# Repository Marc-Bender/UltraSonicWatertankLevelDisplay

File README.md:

# README

##Intended Usecase
Waterlevel display in multitank battey of tanks. Tanks are located in basement, sense device will be mounted on top of tanks far enough away from filling port. 
Thus no watertightness or waterresistance is implemented for any of the components.

## Design Features
Multiple Sensorboards "supported" by design (read Mistakes#J5 for more).
Elaborate Liter-age estimation algorithm by approximation of tank geometry with multiple boxes of varying area, spacing of estimation-box-area-entries parametrizable (1 global value)
Remaining Tankgeometry (Distance when full, distance when empty, number of tanks) parametrizable. 
Measurement sample averaging with parametrizable sample count for general stability, reproducability and compensation of effects of surface-waves while filling (effectiveness not proven)
Sleep modes for powersaving: between user interactions (deepest possible sleep mode), for time that display is supposed to be on (deepest sleep mode that can be left by timer)
Parametrization via UART with ready made tool (Open protocol)

## Operating instructions
Connect battery without pressing the front panel button --> normal startup procedure; system will perform one measurement cycle and show the results on the display
Connect battery with pressed front panel button --> boot into parametrization mode; leave via UART command or powercycle

## Basic-most Troubleshooting 
### "Display stays dark on button press"
Disassembly of sense device, check battery voltage -- system will not attempt any measurements below 7V
When Battery Voltage >7V attempt powercycle (battery disconnect-reconnect)

## Parametrization protocol
### UART Specifics
9600Baud, 8bits, 1 stop bit, no parity
### Leaving the parametrization session
send ":q" (without quotes)
### write a memory location 
send ":wXXYY" where XX is the address in MSB first and YY is the value in MSB first (both 16bit); device will respond with ":WXX00" where XX is that same address and 00 is padding data.
### read a memory location
analogous to write except ":r" is to be used instead of ":w"; data will be in last two response bytes in 16bit MSBFirst
### Memory Map
TankFullCM         | 0x0000 | 2bytes
TankEmptyCM        | 0x0002 | 2bytes
NumTanks           | 0x0004 | 1byte
AreaEntryCount     | 0x0005 | 1byte
AreaEntrySpacingCm | 0x0006 | 1byte
AveragingCount     | 0x0007 | 1byte
SensorType         | 0x0008 | 1byte (0: HC-SR04, 1:Grove)
AreaEntrySpaceStart| 0x000A | 2bytes per entry

## Power Figures
To be powered from a 9V Block Battery. Active current (w/ Display on, sensor not attached) is ~15mA. 
The MCU will be in sleep just about the entire time. The current transient for the MCU being active is assumed to be neglegdable.
The current transient by the sensor has not been determined. But the sensor is powered from IO Pins and normally unpowered thus not adding to the Iq.
The current consumption in sleep (Display off, sensor disconnected, MCU sleep) was in the noise of the multimeter (readings are typical at ~1mV across 10R shunt experimentally put in place instead of regulator; ~100uA)

## Hacking features
Default values for liter estimation algorithm when activated by define but not configured in EEPROM.
Define for circumventing the Battery voltage measurement evaluation -- effectively rendering the BatteryLowFault State inoperable/unreachable.

## Mistakes 

### Parametrization tool 

Somehow the parametrization did not work in the real usecase where the device is powered from a 9V battery; neither with connected gnd nor with connected 5V rail nor both connected (to the usb to serial brigde)
Parametrization also did not work no matter if the TX and RX lines are crossed or not. -- I did not feel like investing any time in this issue anymore, thus did not use the parametrization at all and hardcoded the tank geometry
Circumvent: recompile firmware with different values for each tank geometry or manually generate the eeprom file. 

### voltage measurement 

The battery voltage measurement is wildly off -- this may be down to the reference of the ADC (VCCA) not being measured in any way impacting the measured value...
Circumvent: none

### case design / Assembly design 

the screw holes for the display retainment screws should not have gone through the entire part. 
the Controller PCB should have had any mounting holes. 
The PCB Sandwich should be held in place on the button side as well in some way; solved by drilling through the PCB (somewhere in the gnd plane above the button) and into the frontplate then securing the pcb sandwich with 1 or 2 threads of a screw
The button actuator may collide with the PCB sandwich and should be reshaped.
The Parametrization header's 5V pin is obscured by the lower mounting hole of the display -> circumvent by snipping that off.

### Q5
Reverse voltage Protection "Diode" Transistor (Q5) did not work in my testing.
Circumvent by placing a ordinary diode between pins 1 and 2 of the footprint.

### U2
Was not available to me at the time of building and pinning is unlike 117 or 78xx series regulator thus the device may be a bad pick when a generic jellybean part would be wanted. 
There is no special reason to use this one. 
Circumvent by either buying appropriate part or replace with 7805 mounted in reverse (smaller footprint one will work as current consumption of MCU and display when active is ~15mA in my measurement thus anysize regulator will likely be enough)

### J1
/tRST is connected to MCU but /sRST would be the one to use with standard AVR JTAG pinout. 
Circumvent by either using SPI which is available on the Display header or by shorting the /tRST and /sRST pins together.

### U1
ATmega1284P was initially designed in as it happened to be in my junkbox... later replaced with ATmega324PB as a cheaper more than plenty replacement.
The ATmega324PB is not exactly pin compatible as the two (1284P) supply pins on the bottom edge (17, 18) are IO pins on the 324PB.
Circumvent: none
Fix: new layout or stick with original design MCU. 
Impact: none as long as the SW does not configure the two pins as outputs (which it should not -- by design)

### V0
V0 had been planned to be connected to resistor divider for contrast setting (that is switch-off-able). But fixed 1k pull down would be enough.
Circumvent by not placing R13, R14, R11, Q3 and instead placing R12 as ~500R and placing another ~500R between pins 2 and 3 of Q3 (slight cant).
alternatively only place R12 as 1k and bridge pins 2 and 3 of Q3

### J5 
Pinning of header for Grove Ultrasonic rangefinder module is completely messed up w/ regard to the module. 
Circumvent: use a crossover wireharnes and / or change the pinning in as far as possible (supply pins). Possibly bridge pin 3 and 4 on J5 to fix switched signal and NC pin. 
alternatively stick with HC-SR04 board instead. 
Firmware side of things has not been verified for Grove module at all thus it may require some hacking to get working. 

### Q4 
Technically working how ever not sufficent for turning off the display. The display module will get its power also over the data and control lines if not powered thus setting all data and control lines to input-no-pullup before turning off the display is required.
Circumvent: not needed -- already accounted for in Firmware. 

## Issues
### Parametrization tool communication (General)
Send commands multiple times until a) the display lights up [stop session command] or b) message counter in log window in bottom updates
### Parametrization tool connection
Start the sense device in parametrization mode.
Send the stop command from the tool until successfully left the session. 
Keep the Tool running and connected to the UART to USB adapter.
Restart the sense device in parametrization mode. 
The communciation should now work -- signs of a non working communication are UI buttons not changing their animated state.
### Parametrization best practices
Send a value
set a different value
Read back value --> the UI element for setting doubles for display and should change value to before set value.

Always leave the parametrization session by stop command when values have been changed in order for the write to peristant memory to happen.

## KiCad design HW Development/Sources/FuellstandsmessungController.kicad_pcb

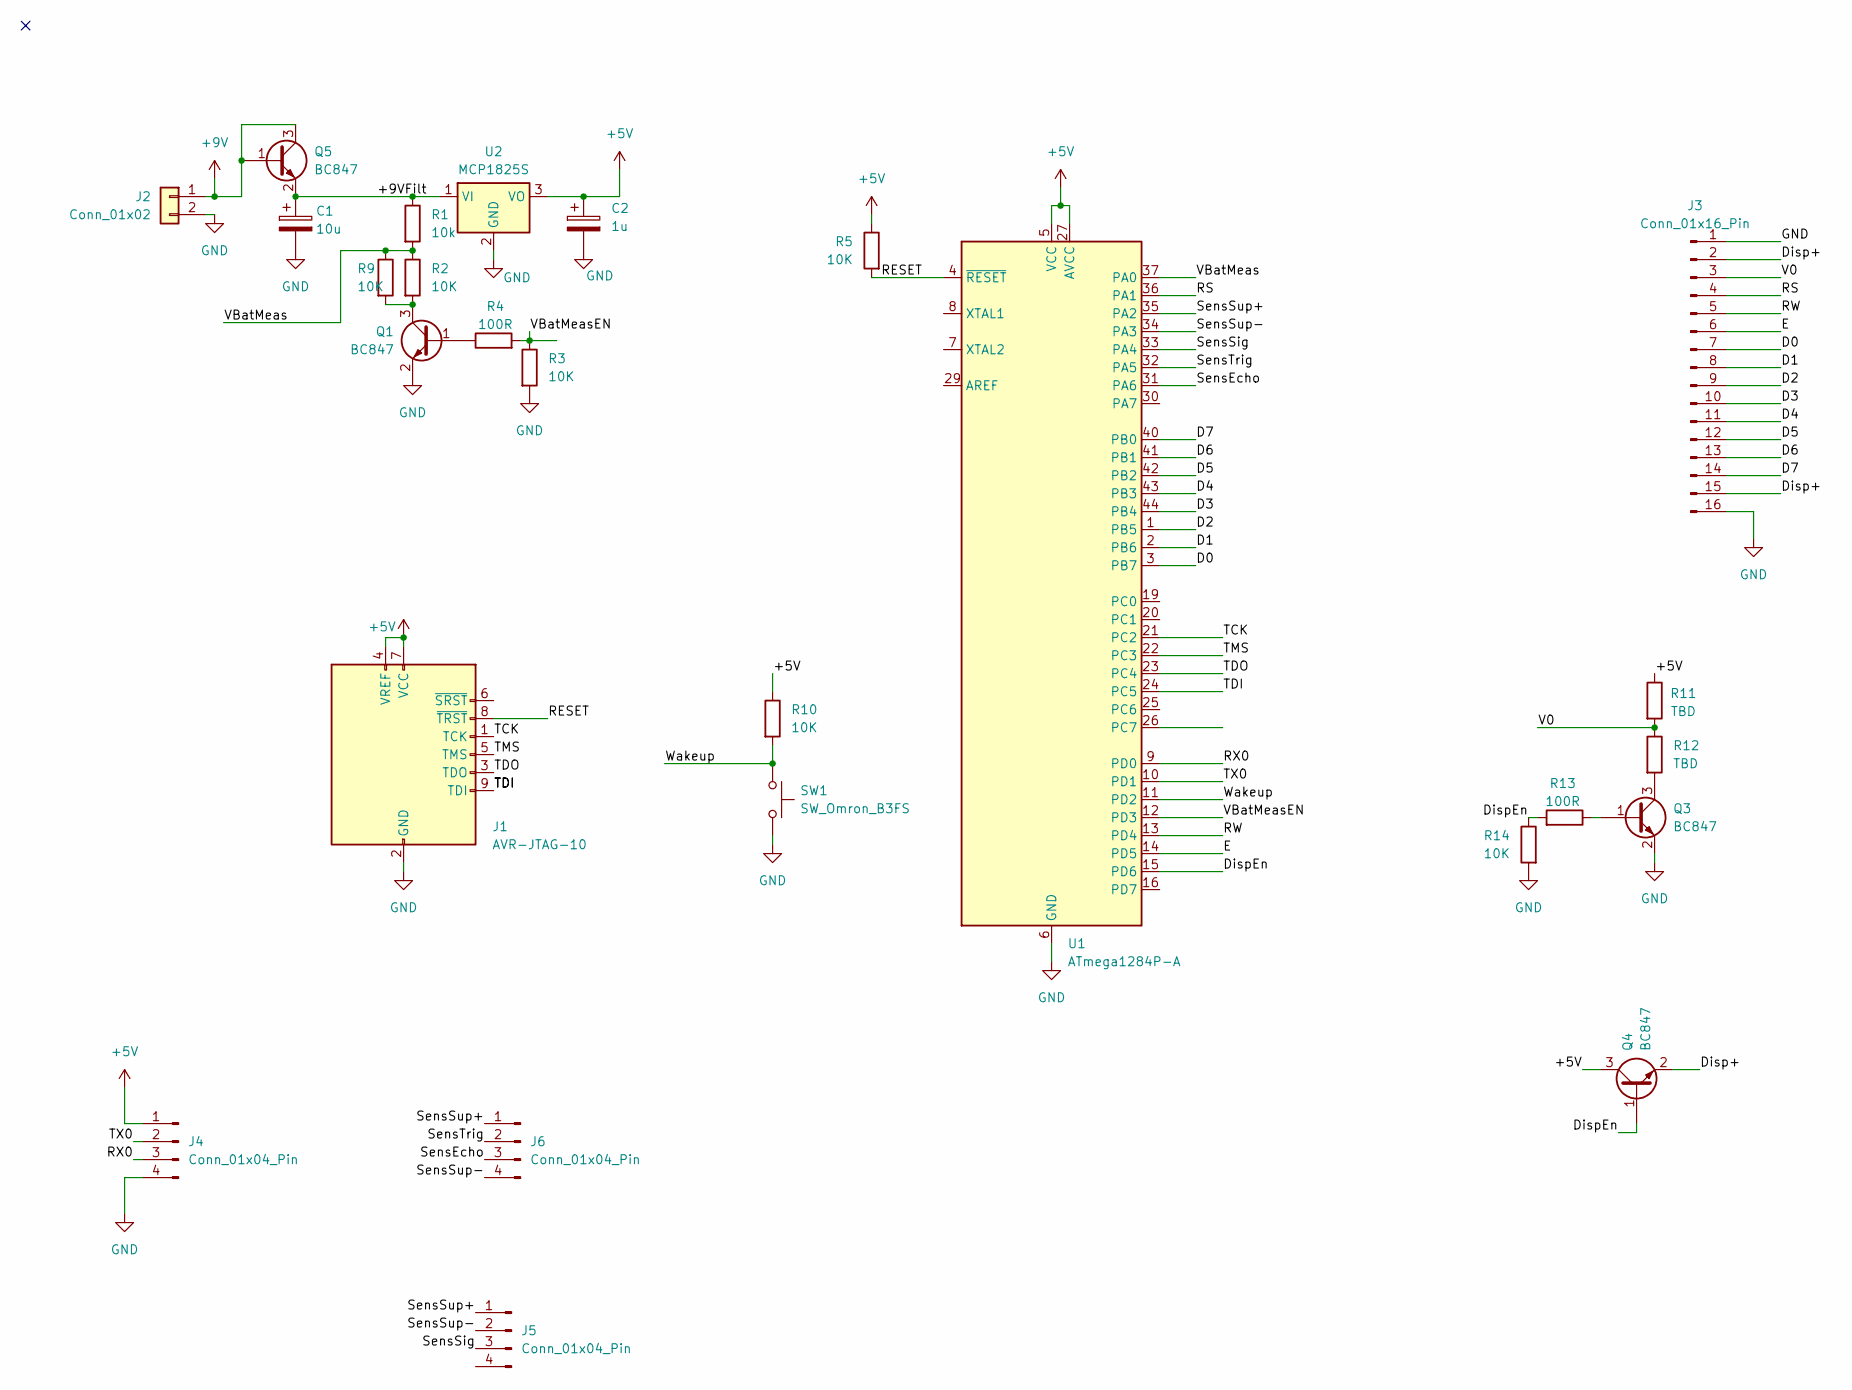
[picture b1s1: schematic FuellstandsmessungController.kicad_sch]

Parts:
C1: 10u; CP_Radial_D5.0mm_P2.50mm
C2: 1u; CP_Radial_D5.0mm_P2.50mm
J1: AVR-JTAG-10; IDC-Header_2x05_P2.54mm_Vertical
J2: Conn_01x02; PinHeader_1x02_P2.54mm_Vertical
J3: Conn_01x16_Pin; PinHeader_1x16_P2.54mm_Vertical
J4, J5, J6: Conn_01x04_Pin; PinHeader_1x04_P2.54mm_Vertical
Q1, Q3, Q4, Q5: BC847; SOT-23
R1: 10k; R_0805_2012Metric_Pad1.20x1.40mm_HandSolder
R2, R3, R5, R9, R10, R14: 10K; R_0805_2012Metric_Pad1.20x1.40mm_HandSolder
R4, R13: 100R; R_0805_2012Metric_Pad1.20x1.40mm_HandSolder
R11, R12: TBD; R_0805_2012Metric_Pad1.20x1.40mm_HandSolder
SW1: SW_Omron_B3FS; SW_SPST_Omron_B3FS-100xP
U1: ATmega1284P-A; TQFP-44_10x10mm_P0.8mm
U2: MCP1825S; SOT-223-3_TabPin2

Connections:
+5V: C2.1, J1.4 (VREF), J1.7 (VCC), J4.1, Q4.3 (C), R5.1, R10.1, R11.1, U1.5 (VCC), U1.17 (VCC), U1.27 (AVCC), U1.38 (VCC), U2.3 (VO)
+9V: J2.1, Q5.1 (B), Q5.3 (C)
/+9VFilt: C1.1, Q5.2 (E), R1.1, U2.1 (VI)
/D0: J3.7, U1.3 (PB7)
/D1: J3.8, U1.2 (PB6)
/D2: J3.9, U1.1 (PB5)
/D3: J3.10, U1.44 (PB4)
/D4: J3.11, U1.43 (PB3)
/D5: J3.12, U1.42 (PB2)
/D6: J3.13, U1.41 (PB1)
/D7: J3.14, U1.40 (PB0)
/Disp+: J3.2, J3.15, Q4.2 (E)
/DispEn: Q4.1 (B), R13.2, R14.1, U1.15 (PD6)
/E: J3.6, U1.14 (PD5)
/RESET: J1.8 (~TRST), R5.2, U1.4 (~RESET)
/RS: J3.4, U1.36 (PA1)
/RW: J3.5, U1.13 (PD4)
/RX0: J4.3, U1.9 (PD0)
/SensEcho: J6.3, U1.31 (PA6)
/SensSig: J5.3, U1.33 (PA4)
/SensSup+: J5.1, J6.1, U1.35 (PA2)
/SensSup-: J5.2, J6.4, U1.34 (PA3)
/SensTrig: J6.2, U1.32 (PA5)
/TCK: J1.1 (TCK), U1.21 (PC2)
/TDI: J1.9 (TDI), U1.24 (PC5)
/TDO: J1.3 (TDO), U1.23 (PC4)
/TMS: J1.5 (TMS), U1.22 (PC3)
/TX0: J4.2, U1.10 (PD1)
/V0: J3.3, R11.2, R12.1
/VBatMeas: R1.2, R2.1, R9.1, U1.37 (PA0)
/VBatMeasEN: R3.1, R4.2, U1.12 (PD3)
/Wakeup: R10.2, SW1.1, U1.11 (PD2)
GND: C1.2, C2.2, J1.2 (GND), J1.10 (GND), J2.2, J3.1, J3.16, J4.4, Q1.2 (E), Q3.2 (E), R3.2, R14.2, SW1.2, U1.6 (GND), U1.18 (GND), U1.28 (GND), U1.39 (GND), U2.2 (GND)
unnamed: Q1.1 (B), R4.1
unnamed: Q1.3 (C), R2.2, R9.2
unnamed: Q3.1 (B), R13.1
unnamed: Q3.3 (C), R12.2

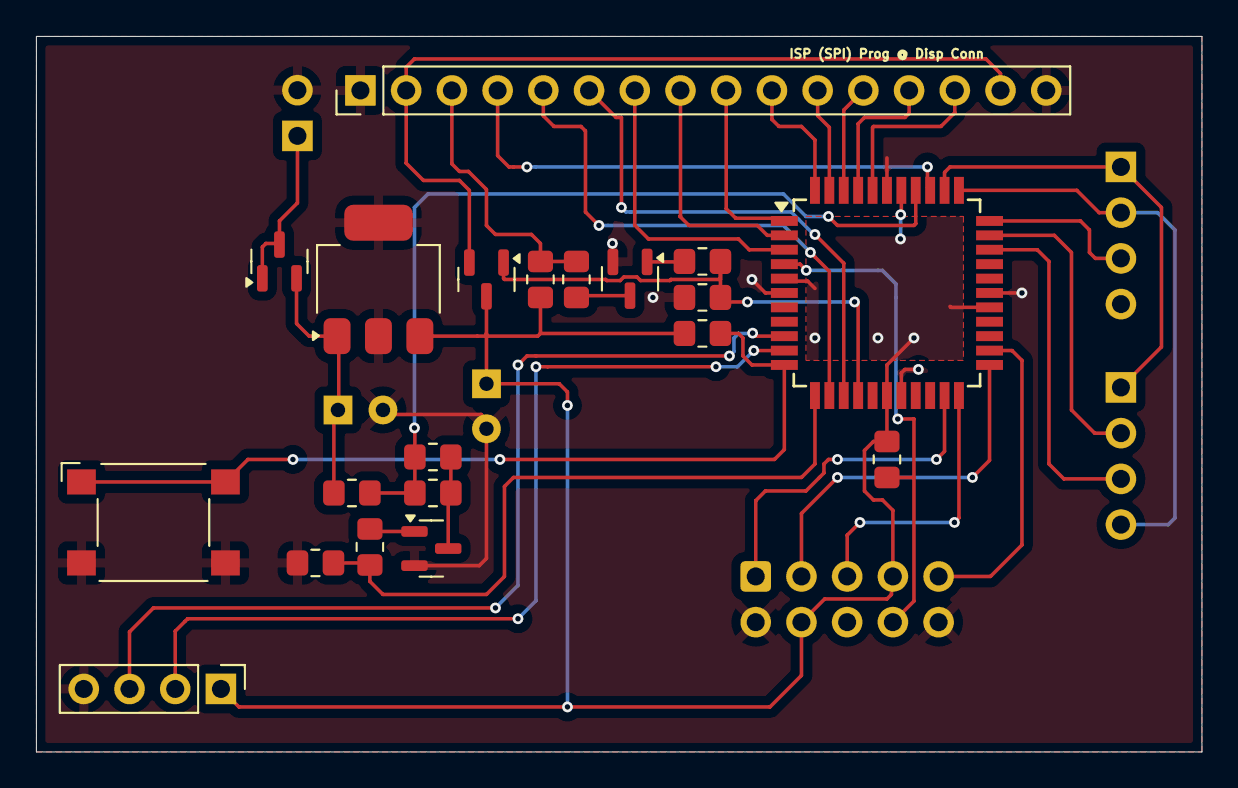
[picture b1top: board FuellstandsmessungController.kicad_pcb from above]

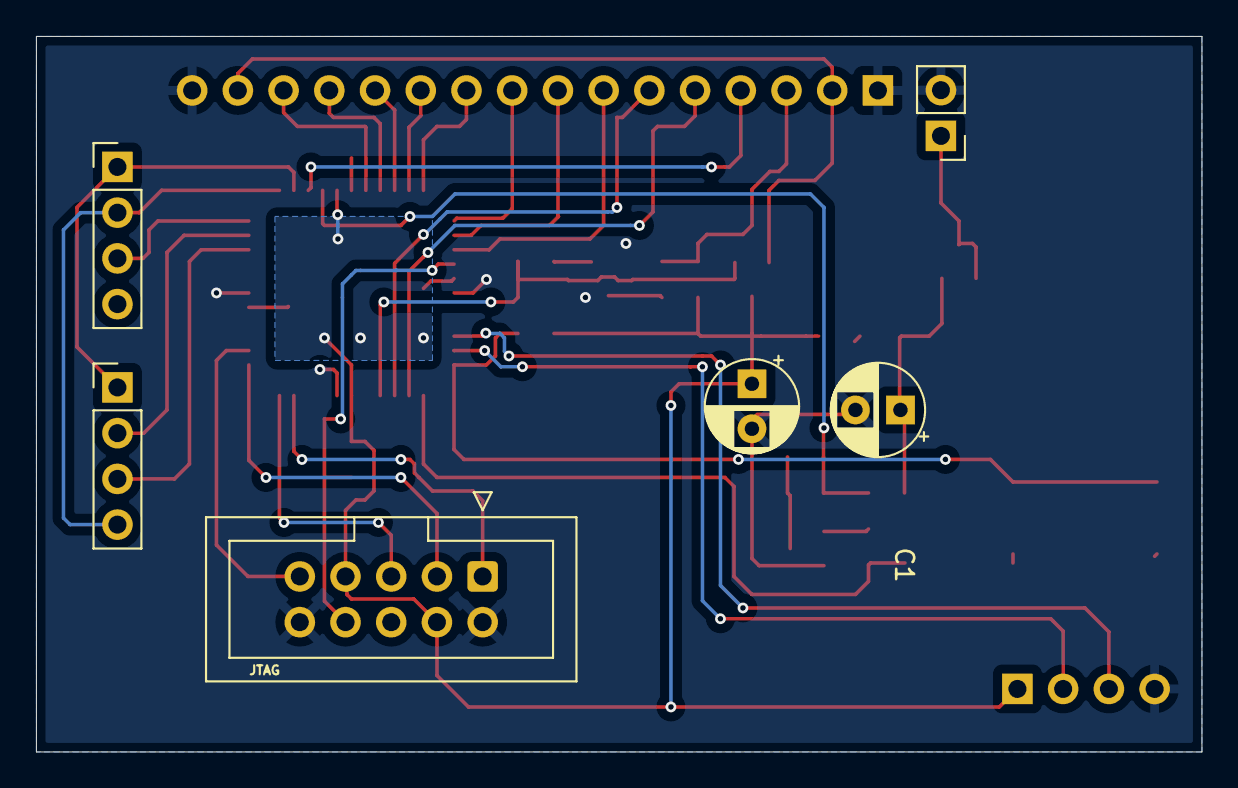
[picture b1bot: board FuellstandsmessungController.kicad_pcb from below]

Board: 2 copper layers, 64.8 x 39.8 mm, 26 parts (6 on the bottom side), 37 nets.

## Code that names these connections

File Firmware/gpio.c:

/*
 * gpio.c
 *
 * Created: 19.05.2024 15:46:27
 *  Author: marc
 */ 

#include "gpio.h"
#include <avr/io.h>
#include <stdbool.h>

#define ARDUINO (0)

GPIO_t pins[] = 
{
#if ARDUINO == 0
	{&PORTA,&DDRA,&PINA,0, false}, // vbat meas
	{&PORTA,&DDRA,&PINA,1, true}, // rs
	{&PORTA,&DDRA,&PINA,2, true}, // sup+
	{&PORTA,&DDRA,&PINA,3, true}, // sup-
	{&PORTA,&DDRA,&PINA,4, false}, // senssig
	{&PORTA,&DDRA,&PINA,5, true}, // senstrig
	{&PORTA,&DDRA,&PINA,6, false}, // sensecho
              
	{&PORTB,&DDRB,&PINB,0, true}, // d7
	{&PORTB,&DDRB,&PINB,1, true}, // d6
	{&PORTB,&DDRB,&PINB,2, true}, // d5
	{&PORTB,&DDRB,&PINB,3, true}, // d4
	{&PORTB,&DDRB,&PINB,4, true}, // d3
	{&PORTB,&DDRB,&PINB,5, true}, // d2
	{&PORTB,&DDRB,&PINB,6, true}, // d1
	{&PORTB,&DDRB,&PINB,7, true}, // d0
              
	{&PORTD,&DDRD,&PIND,0, false}, // rx
	{&PORTD,&DDRD,&PIND,1, true}, // tx
	{&PORTD,&DDRD,&PIND,2, false}, // wakeup
	{&PORTD,&DDRD,&PIND,3, true}, // vbatmeasen
	{&PORTD,&DDRD,&PIND,4, true}, // rw
	{&PORTD,&DDRD,&PIND,5, true}, // en
	{&PORTD,&DDRD,&PIND,6, true}, // dispen
#else // ARDUINO == 1
	{&PORTF,&DDRF,&PINF,0, false}, // vbat meas
	{&PORTL,&DDRL,&PINL,3, true}, // rs
	{&PORTF,&DDRF,&PINF,1, true}, // sup+
	{&PORTF,&DDRF,&PINF,2, true}, // sup-
	{&PORTF,&DDRF,&PINF,3, false}, // senssig
	{&PORTF,&DDRF,&PINF,4, true}, // senstrig
	{&PORTF,&DDRF,&PINF,5, false}, // sensecho
              
	{&PORTA,&DDRA,&PINA,4, true}, // d7
	{&PORTA,&DDRA,&PINA,6, true}, // d6
	{&PORTC,&DDRC,&PINC,7, true}, // d5
	{&PORTC,&DDRC,&PINC,5, true}, // d4
	{&PORTC,&DDRC,&PINC,3, true}, // d3
	{&PORTC,&DDRC,&PINC,1, true}, // d2
	{&PORTD,&DDRD,&PIND,7, true}, // d1
	{&PORTG,&DDRG,&PING,1, true}, // d0
              
	{&PORTE,&DDRE,&PINE,0, false}, // rx
	{&PORTE,&DDRE,&PINE,1, true}, // tx
	{&PORTD,&DDRD,&PIND,0, false}, // wakeup
	{&PORTK,&DDRK,&PINK,0, true}, // vbatmeasen
	{&PORTL,&DDRL,&PINL,5, true}, // rw
	{&PORTL,&DDRL,&PINL,7, true}, // en
	{&PORTF,&DDRF,&PINF,6, true}, // dispen
#endif
};

void GPIO_SensSigPinReinit(void)
{
	*(pins[SensSig].ddr) &= ~(1<<(pins[SensSig].pinnumber)); // make input before possibly changing to output

	if(pins[SensSig].isOutput == true)
	{
		*(pins[SensSig].ddr) |= 1<<(pins[SensSig].pinnumber);
	}
	else
	{
		// input already set by preclear
	}
}

void GPIO_DPinReinit(void)
{
	for(uint8_t i=D7;i<=D0;i++)
	{
		*(pins[i].ddr) &= ~(1<<(pins[i].pinnumber)); // make input before possibly changing to output
		if(pins[i].isOutput == true)
		{
			*(pins[i].ddr) |= 1<<(pins[i].pinnumber);
		}
		else
		{
			// input already set by preclear
		}
	}
}

void GPIO_init(void)
{
	for(uint8_t i=0;i<PINS_COUNT;i++)
	{
		*(pins[i].ddr) &= ~(1<<(pins[i].pinnumber)); // make input before possibly changing to output
		if(pins[i].isOutput == true)
		{
			*(pins[i].ddr) |= 1<<(pins[i].pinnumber);
		}
		else
		{
			// input already set by preclear
		}
	}
	#if ARDUINO == 1
		DDRB |= 1<<1; // supply display logic -
		DDRB |= 1<<3; // supply display logic +
		DDRA |= 1<<2; // supply backlight +
		DDRA |= 1<<0; // supply backlight -
		PORTB &= ~(1<<1); // supply display logic - == low
		PORTB |= 1<<3; // supply display logic + == high
		PORTA |= 1<<2; // supply backlight + == high
		PORTA &= ~(1<<0);// supply backlight - == low
	#endif
}

static void GPIO_setPinTo(const pins_e whichPin, const bool enable)
{
	const uint8_t mask = 1<<pins[whichPin].pinnumber;
	*(pins[whichPin].port) &= ~mask;
	if(enable == true)
	{
		*(pins[whichPin].port) |= mask;
	}
	else
	{
		// not to be set high thus keep at low as done by nand before if else
	}
}

void GPIO_setVBatMeasEn_to(const bool enable)
{
	GPIO_setPinTo(VBatMeasEn,enable);
}

void GPIO_setRW_to(const bool enable)
{
	GPIO_setPinTo(RW,enable);
}

void GPIO_setE_to(const bool enable)
{
	GPIO_setPinTo(EN,enable);
}

void GPIO_setDispEn_to(const bool enable)
{
#if 0
	if(
		   (enable) 
		 &&((*(pins[DispEn].ddr) & (1<<(pins[DispEn].pinnumber))) != 0) // shall be high and is output (ie. output low) --> make input pullup ie high
	  )
	{
		*(pins[DispEn].ddr) &= ~(1<<(pins[DispEn].pinnumber));
		*(pins[DispEn].port) |= 1<<(pins[DispEn].pinnumber);
	}
	else if(enable)
	{
		// should be high and is input pullup .. nothing to do
	}
	else if(
				  (!enable) // should be low but is input pullup ie high
				&&((*(pins[DispEn].ddr) & (1<<(pins[DispEn].pinnumber))) == 0)
	       )
	{
		*(pins[DispEn].ddr) |= (1<<(pins[DispEn].pinnumber));
		*(pins[DispEn].port) &= ~(1<<(pins[DispEn].pinnumber));
	}
	else
	{
		// should be low and is low... nothing to do
	}
#else
	GPIO_setPinTo(DispEn,enable);
#endif
}

void GPIO_setRS_to(const bool enable)
{
	GPIO_setPinTo(RS,enable);
}

void GPIO_setSensSupP_to(const bool enable)
{
	GPIO_setPinTo(SupP,enable);
}

void GPIO_setSensSupM_to(const bool enable)
{
	GPIO_setPinTo(SupM,enable);
}

void GPIO_setSensTrig_to(const bool enable)
{
	GPIO_setPinTo(SensTrig,enable);
}

void GPIO_setSensSig_to(const bool enable)
{
	GPIO_setPinTo(SensSig,enable);
}

void GPIO_setDPins_to(const uint8_t value)
{
	for(uint8_t i=0;i<8;i++)
	{
		if((value & (1<<i)) != 0)
		{
			GPIO_setPinTo(D0-i,true);
		}
		else
		{
			GPIO_setPinTo(D0-i,false);
		}
	}
}

uint8_t GPIO_getPin(const pins_e whichPin) //< 1 = high 0=low
{
	return (((*pins[whichPin].pin)&(1<<pins[whichPin].pinnumber))!=0)?1:0;
}

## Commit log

2024-07-02 initial commit for HW, embSW & pcSW
2024-07-02 Add extensive README and Mechanical design files
2024-09-13 update mechanical files
2024-12-14 redesign the entire casing to get away without having to use the retainment clips behind the PCB Sandwich (which turned out to be an assembly nightmare) also redesign the casing such that it actually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
    change the firmware such that the tank geometry of the tanks this was designed for is used by default b/c the parametrization did not work as intended.
2024-12-14 explain more mistakes being made in the README
